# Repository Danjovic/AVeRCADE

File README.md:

# AVeRCADE
Customisable USB adapter for arcade controls.

AVeRCADE is a flexible USB adapter for arcade controls based on AVR and V-USB. It can also work as a generic development board, since it uses USBaspLoader to update the firmware.

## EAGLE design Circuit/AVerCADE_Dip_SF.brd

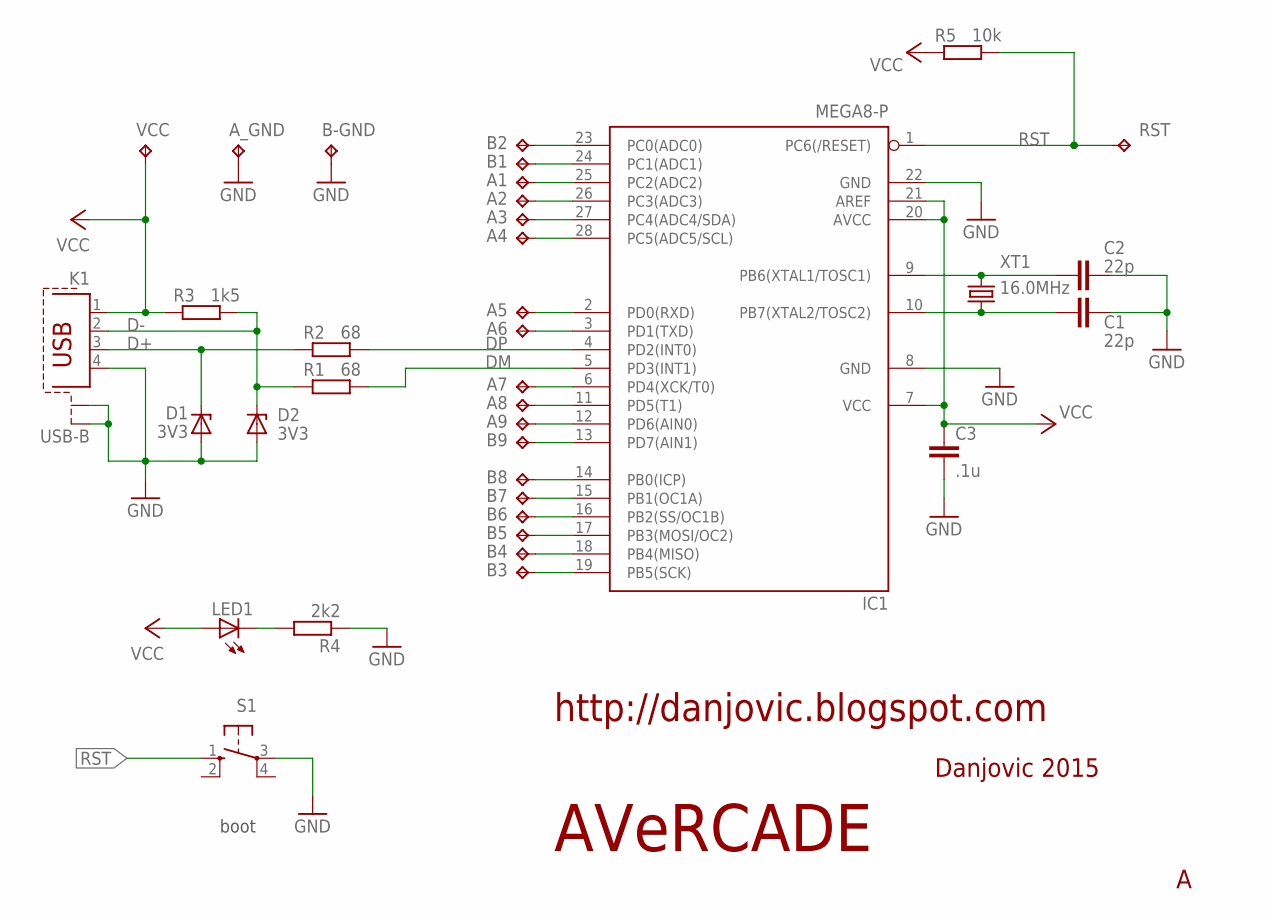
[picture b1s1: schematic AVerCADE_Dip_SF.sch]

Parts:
A1, A2, A3, A4, A5, A6, A7, A8, A9: TPPAD1-13; P1-13
A_GND: TPPAD1-13; P1-13
B1, B2, B3, B4, B5, B6, B7, B8, B9: TPPAD1-13; P1-13
B-GND: TPPAD1-13; P1-13
C1, C2: 22p; C025-24X044L
C3: .1u; C050-025X075L
D1, D2: 3V3; ZDIO-5L
IC1: MEGA8-P; DIL28-3
K1: USB-B; PN61729-SL
LED1: LEDLED3MML; LED3MML
R1, R2: 68; 0207/7L
R3: 1k5; 0207/7L
R4: 2k2; 0207/7L
R5: 10k; 0207/7L
RST: TPPAD1-13; P1-13
S1: 10-XX; B3F-10XX
VCC: TPPAD1-13; P1-13
XT1: 16.0MHz; HC49U-V

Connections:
AN2: A1.TP, IC1.25 (PC2(ADC2))
AN3: A2.TP, IC1.26 (PC3(ADC3))
D+: D1.C, K1.3, R2.3 (1)
D-: D2.C, K1.2, R1.3 (1), R3.4 (2)
DM: IC1.5 (PD3(INT1)), R1.4 (2)
DP: IC1.4 (PD2(INT0)), R2.4 (2)
GND: A_GND.TP, B-GND.TP, C1.2, C2.2, C3.2, D1.A, D2.A, IC1.8 (GND), IC1.22 (GND), K1.4, K1.S1, K1.S2, R4.3 (1), S1.3
unnamed: A5.TP, IC1.2 (PD0(RXD))
unnamed: A7.TP, IC1.6 (PD4(XCK/T0))
unnamed: B1.TP, IC1.24 (PC1(ADC1))
unnamed: B2.TP, IC1.23 (PC0(ADC0))
unnamed: A3.TP, IC1.27 (PC4(ADC4/SDA))
unnamed: A4.TP, IC1.28 (PC5(ADC5/SCL))
unnamed: A6.TP, IC1.3 (PD1(TXD))
unnamed: A8.TP, IC1.11 (PD5(T1))
unnamed: A9.TP, IC1.12 (PD6(AIN0))
unnamed: B9.TP, IC1.13 (PD7(AIN1))
unnamed: LED1.K (C), R4.4 (2)
unnamed: B8.TP, IC1.14 (PB0(ICP))
unnamed: B6.TP, IC1.16 (PB2(SS/OC1B))
unnamed: B7.TP, IC1.15 (PB1(OC1A))
unnamed: B3.TP, IC1.19 (PB5(SCK))
unnamed: B4.TP, IC1.18 (PB4(MISO))
unnamed: B5.TP, IC1.17 (PB3(MOSI/OC2))
RST: IC1.1 (PC6(/RESET)), R5.4 (2), RST.TP, S1.1 (S)
VCC: C3.1, IC1.7 (VCC), IC1.20 (AVCC), IC1.21 (AREF), K1.1, LED1.A, R3.3 (1), R5.3 (1), VCC.TP
X1: C2.1, IC1.9 (PB6(XTAL1/TOSC1)), XT1.2
X2: C1.1, IC1.10 (PB7(XTAL2/TOSC2)), XT1.1

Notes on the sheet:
boot
Danjovic 2015
AVeRCADE
http://danjovic.blogspot.com

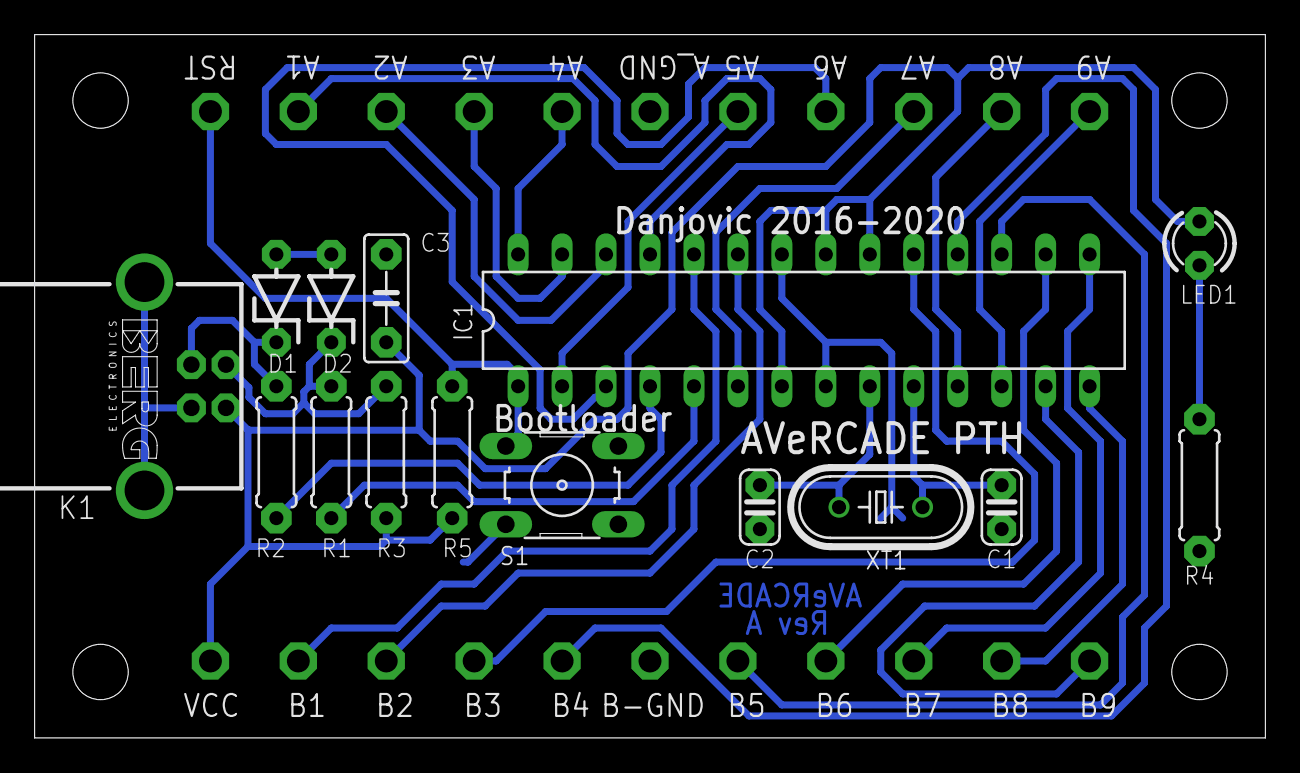
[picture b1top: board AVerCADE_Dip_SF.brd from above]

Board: 2 copper layers, 71.1 x 40.6 mm, 37 parts (0 on the bottom side), 28 nets.

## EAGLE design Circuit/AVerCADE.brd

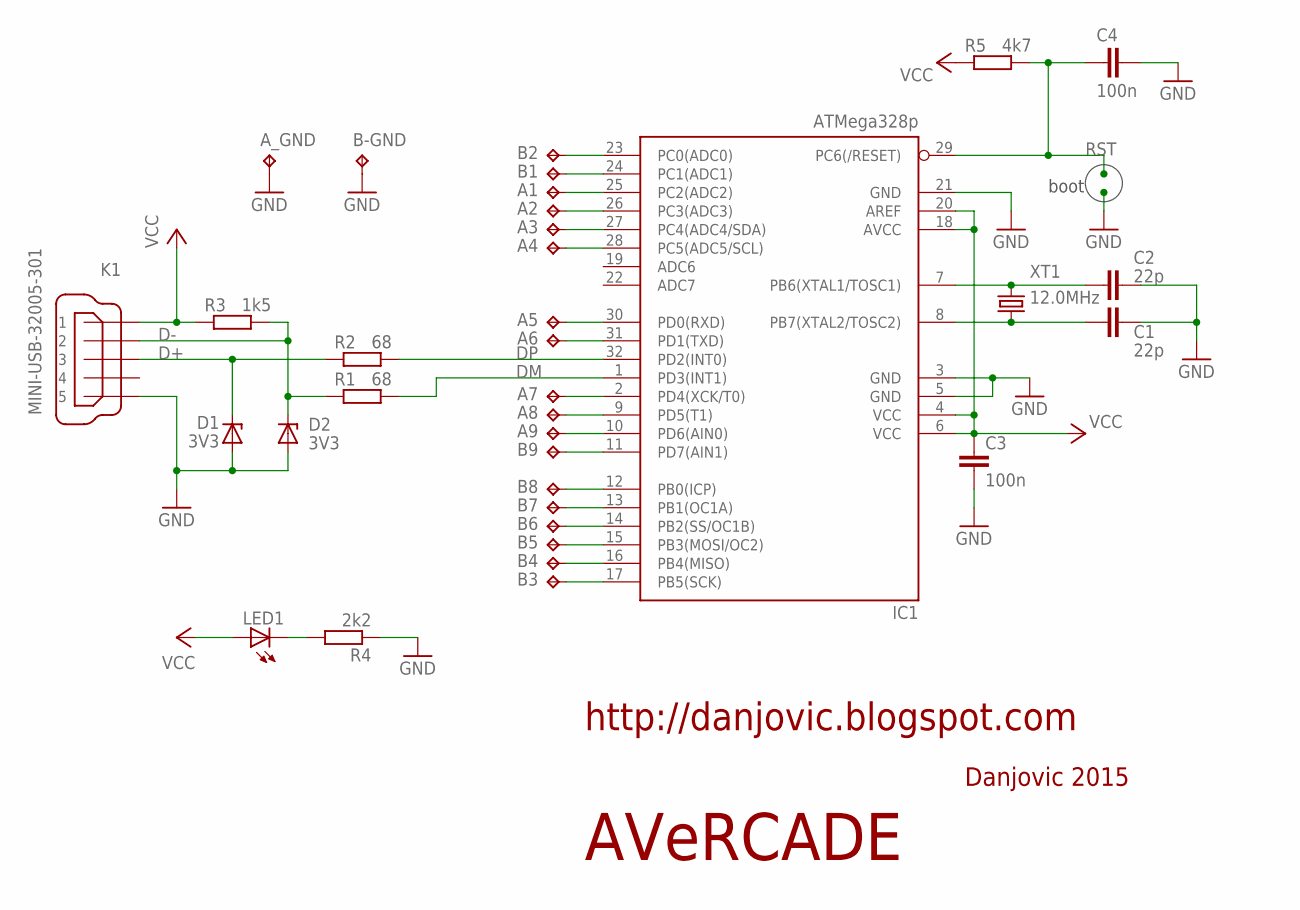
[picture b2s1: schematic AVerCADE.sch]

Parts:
A1, A2, A3, A4, A5, A6, A7, A8, A9: TPPAD1-13; P1-13
A_GND: TPPAD1-13; P1-13
B1, B2, B3, B4, B5, B6, B7, B8, B9: TPPAD1-13; P1-13
B-GND: TPPAD1-13; P1-13
C1, C2: 22p; C0805
C3, C4: 100n; C1206
D1, D2: 3V3; SOD80C
IC1: ATMega328p; TQFP32-08
K1: MINI-USB-32005-301; 32005-301
LED1: LEDSML1206; SML1206
R1, R2: 68; M1206
R3: 1k5; M1206
R4: 2k2; M1206
R5: 4k7; M1206
XT1: 12.0MHz; HC49UP

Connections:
AN2: A1.TP, IC1.25 (PC2(ADC2))
AN3: A2.TP, IC1.26 (PC3(ADC3))
D+: D1.C, K1.3, R2.1
D-: D2.C, K1.2, R1.1, R3.2
DM: IC1.1 (PD3(INT1)), R1.2
DP: IC1.32 (PD2(INT0)), R2.2
GND: A_GND.TP, B-GND.TP, C1.2, C2.2, C3.2, C4.2, D1.A, D2.A, IC1.3 (GND), IC1.5 (GND), IC1.21 (GND), K1.5, R4.1
unnamed: A5.TP, IC1.30 (PD0(RXD))
unnamed: A7.TP, IC1.2 (PD4(XCK/T0))
unnamed: B1.TP, IC1.24 (PC1(ADC1))
unnamed: B2.TP, IC1.23 (PC0(ADC0))
unnamed: A3.TP, IC1.27 (PC4(ADC4/SDA))
unnamed: A4.TP, IC1.28 (PC5(ADC5/SCL))
unnamed: A6.TP, IC1.31 (PD1(TXD))
unnamed: A8.TP, IC1.9 (PD5(T1))
unnamed: A9.TP, IC1.10 (PD6(AIN0))
unnamed: B9.TP, IC1.11 (PD7(AIN1))
unnamed: LED1.C, R4.2
unnamed: B8.TP, IC1.12 (PB0(ICP))
unnamed: B6.TP, IC1.14 (PB2(SS/OC1B))
unnamed: B7.TP, IC1.13 (PB1(OC1A))
unnamed: B3.TP, IC1.17 (PB5(SCK))
unnamed: B4.TP, IC1.16 (PB4(MISO))
unnamed: B5.TP, IC1.15 (PB3(MOSI/OC2))
RST: C4.1, IC1.29 (PC6(/RESET)), R5.2
VCC: C3.1, IC1.4 (VCC), IC1.6 (VCC), IC1.18 (AVCC), IC1.20 (AREF), K1.1, LED1.A, R3.1, R5.1
X1: C2.1, IC1.7 (PB6(XTAL1/TOSC1)), XT1.2
X2: C1.1, IC1.8 (PB7(XTAL2/TOSC2)), XT1.1

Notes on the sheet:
boot
Danjovic 2015
AVeRCADE
http://danjovic.blogspot.com

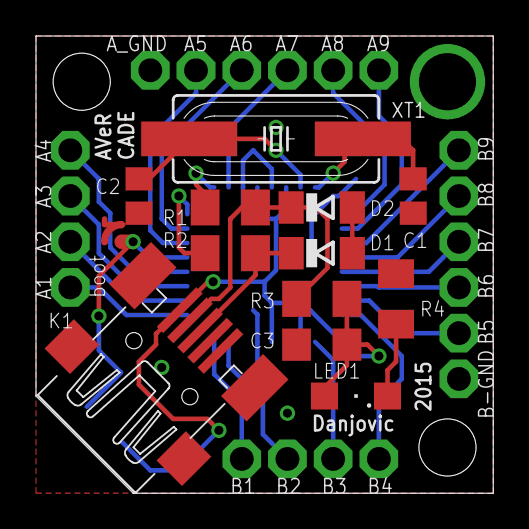
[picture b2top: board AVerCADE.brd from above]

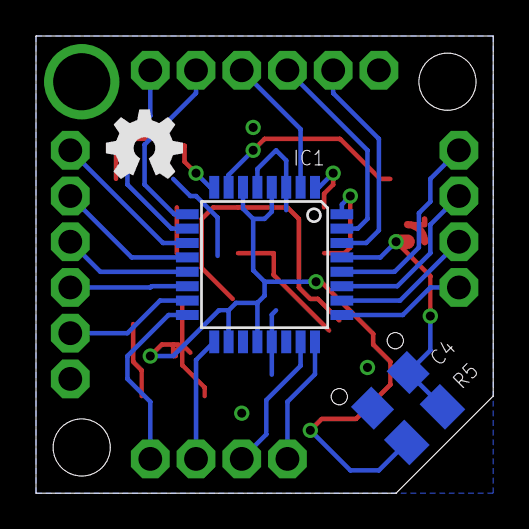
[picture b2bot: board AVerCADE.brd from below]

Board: 2 copper layers, 25.4 x 25.4 mm, 35 parts (3 on the bottom side), 28 nets.

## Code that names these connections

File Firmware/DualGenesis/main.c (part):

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#define B9 bit_is_clear(PIND,7)

// Macros for Genesis controllers
#define GENESIS_1_SELECT_LOW()  PORTC &= ~(1<<PC5)
#define GENESIS_1_SELECT_HIGH() PORTC |=  (1<<PC5)
#define GENESIS_2_SELECT_LOW()  PORTB &= ~(1<<PB4)
#define GENESIS_2_SELECT_HIGH() PORTB |=  (1<<PB4)

// Compatibility with ATMEGA8
#ifndef TCCR0B
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	wdt_disable(); // no watchdog, just because I'm lazy
    
	// Configure I/O PORTS - All Digital Inputs (ARCADE)
	DDRB = (1<<4);  // PB4 as output
	DDRC = (1<<5); // PC5 as output
	DDRD = 0;
	// Configure Pullups except for Pins PD2 and PD3
	PORTB = 0xff;
	PORTC = 0xff;
	PORTD = 0xf3;      // 1 1 1 1 0 0 1 1
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AVeRCADE pin mapping

NAME	AVR_PORT	FUNCTION		
A1		   PC2		
A2		   PC3		
A3		   PC4		GEN1_START_C
A4		   PC5		GEN1_SELECT      (output)
A5		   PD0		GEN1_A_B
A6		   PD1		GEN1_RIGHT_0
A7		   PD4		GEN1_LEFT_0_X
A8		   PD5		GEN1_DOWN_DOWN_Y
A9		   PD6		GEN1_UP_UP_Z
	
B1		   PC1		
B2		   PC0		
B3		   PB5		GEN2_START_C
B4		   PB4		GEN2_SELECT      (output)
B5		   PB3		GEN2_A_B
B6		   PB2		GEN2_RIGHT_0
B7		   PB1		GEN2_LEFT_0_X
B8		   PB0		GEN2_DOWN_DOWN_Y
B9		   PD7		GEN2_UP_UP_Z


#  Sega Genesis 6 Buttton Protocol
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
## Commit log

2015-11-21 :space_invader: Added .gitattributes
2015-11-21 Creation of repository
    Repository created at current stage of development
2015-11-27 Added fuse configuration for ATMEGA8
2015-11-28 Added License files
2015-12-04 Corrected Makefiles for ATMEGA8 @ 16MHz
2015-12-21 Added Dual Atari configuration
    Added support for dual atari controllers with support for Paddles
2016-02-06 Added USBasp Firmware option
2016-07-14 Optimization of directory structure
    Cleanup and optimization of directory structure. Most of firmwares now
    use the latest version of V-USB (2012). The hex files are generated now
    on a "bin" folder.
2016-07-22 Added firmware for dual Sega Genesis, 6 button
2016-07-22 Update main.c for compatibility with ATMega8
2016-07-26 Added singlesided board w/ through hole components
2016-07-28 Enhanced PTH board for homemade built.
    The component pads have been enlarged to ease the home built versions of the board.
2017-03-07 Update Makefile
    Fix missing of directories 'bin' and 'output'
2017-03-07 Update Makefile
2017-03-25 Debouncing added to Digital firmware
    Added timed sample of buttons (16ms) as a countermeasure for contact bouncing.
2020-06-06 Added bootloader invoke button, increased clearance on LED pads
